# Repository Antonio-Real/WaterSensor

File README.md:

# **WaterSensor project**
 Wireless sensor for monitoring the level of a remote water tank.

 The motivation for this small home project came from the need to monitor the water level of a water tank used for watering. When the tank empties it causes air to fill the pipes and hoses, making it a bit of a pain to get out. With this system its easier to know when the tank is about to empty and flip a switch to turn on a water pump (in the future this system will automatically control the pump).

 ## **System overview**

In simple terms, the water level is read by a HC-SR04 ultrasonic sensor which works well on water and doesn't corrode like those contact sensors you dip into water. The sensor data is acquired by a ESP32 and sent to a second ESP32 in another location using ESP-NOW which works well over longer distances and has smaller overhead than WIFI. The water level is then displayed on a standard 16x02 LCD.

One of the challenges of the system came from the fact that the water tank is in a place with no power, so a solar panel made sense to power the sensor and microcontroller. A charge controller and a Lipo battery work together with the solar panel to regulate power to a stable 5V and provide power in periods of no sun. The ESP32 sender board was custom designed to have minimal components to save battery.

## **Materials/tools used**

- 5W Solar panel and solar power management module bought from [Waveshare](https://www.waveshare.com/solar-power-manager.htm).
- 1800 mAh Lipo battery.
- Custom designed ESP32 board.
- HC-SR04 Ultrasonic sensor.
- A second generic ESP32 board + 16x02 LCD.
- Creality Ender 3v2 for printing the enclosures for the PCB, sensor and power module to protect from dust.

## **Repository contents**

| Folder/Files           | Description                                                                          |
| ---------------------- | ------------------------------------------------------------------------------------ |
| [pcb](/pcb)            | Details and CAD files of the custom ESP32 board made for this project                |
| [firmware](/firmware)  | Firmware of both the receiver and sender ESP32 boards                                |
| [models](/models)      | STL files of the 3D printed parts for the enclosures                                 |

## **Pictures**

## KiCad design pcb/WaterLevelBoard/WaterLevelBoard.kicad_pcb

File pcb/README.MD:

# **Wireless sensor board**

This PCB design was kept to a minimum in order to optimize power consumption since it will function on a lipo battery. The main features:

- AP2112 3.3V low dropout (~50mV drop at 100mA) regulator to step down from the 5V that comes from the battery circuit.
- ESP32 microcontroller responsible for reading the HC-SR04 sensor and sending it through ESP-NOW protocol to a second ESP32.
- Screw terminals to easily connect the battery and the HC-SR04 ultrasonic sensor.

The PCB was designed using **Kicad 5.99** nightly build (soon to be released as Kicad 6).

 <br/><br/>

## **Schematic**

## **3D render of the PCB**

## **Manufactured PCB**
The PCB was manufactured in a PCB milling machine and unfortunately came out poorly and required some enameled wire to replace the damaged tracks.

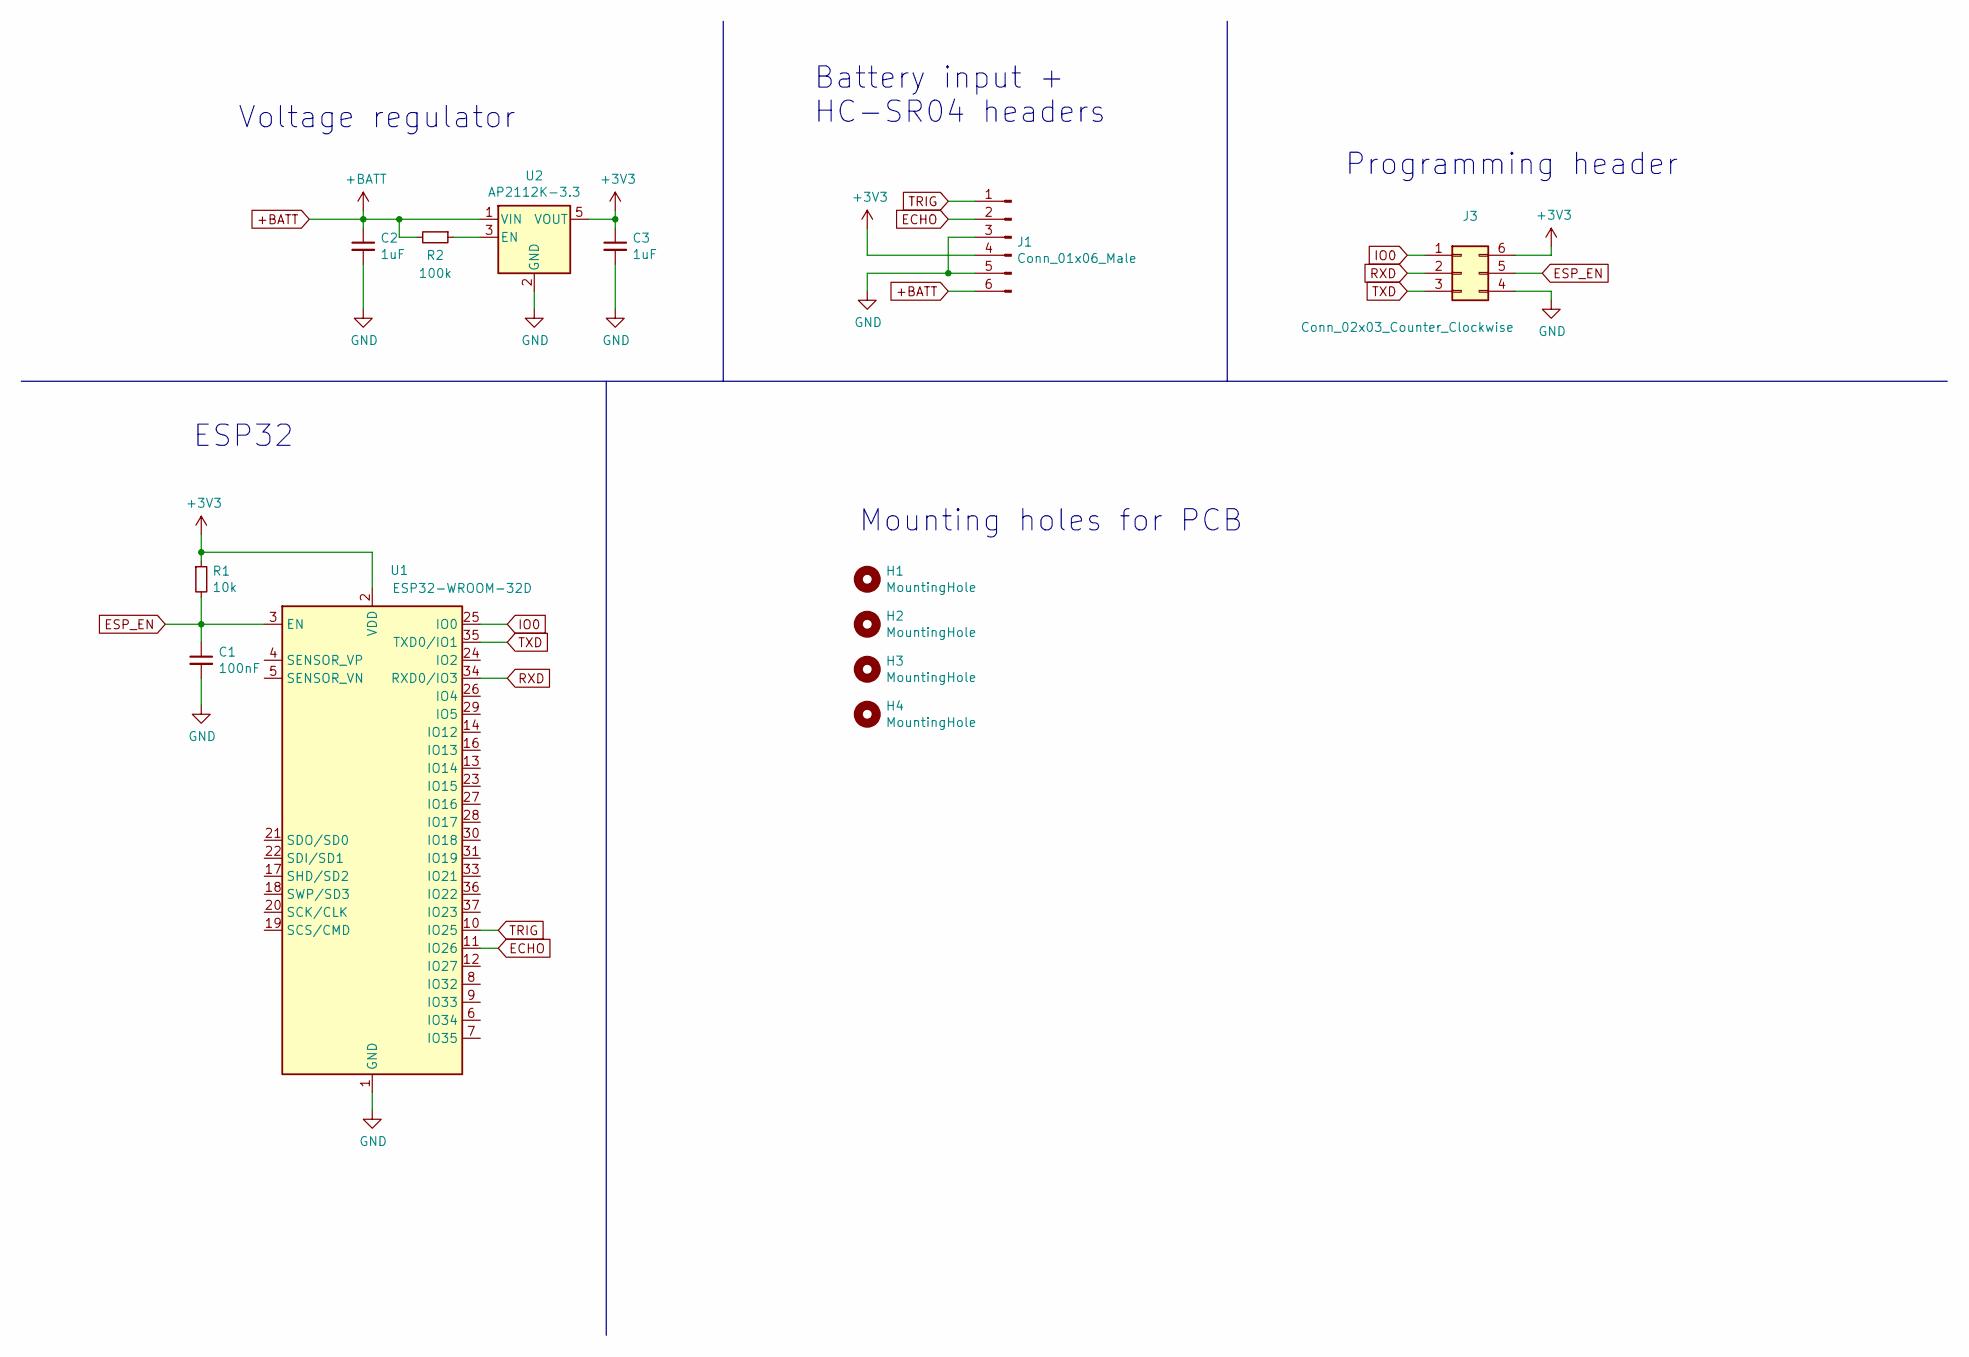
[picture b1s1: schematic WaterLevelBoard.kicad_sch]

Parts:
C1: 100nF; C_0603_1608Metric_Pad1.08x0.95mm_HandSolder
C2, C3: 1uF; C_0603_1608Metric_Pad1.08x0.95mm_HandSolder
H1, H2, H3, H4: MountingHole; MountingHole_2.1mm
J1: Conn_01x06_Male; TerminalBlock_Phoenix_MPT-0,5-6-2.54_1x06_P2.54mm_Horizontal
J3: Conn_02x03_Counter_Clockwise; PinHeader_1x06_P2.54mm_Vertical
R1: 10k; R_0603_1608Metric_Pad0.98x0.95mm_HandSolder
R2: 100k; R_0603_1608Metric_Pad0.98x0.95mm_HandSolder
U1: ESP32-WROOM-32D; ESP32-WROOM-32
U2: AP2112K-3.3; SOT-23-5

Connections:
+3V3: C3.1, J1.4, J3.6, R1.1, U1.2 (VDD), U2.5 (VOUT)
+BATT: C2.1, J1.6, R2.2, U2.1 (VIN)
ECHO: J1.2, U1.11 (IO26)
ESP_EN: C1.1, J3.5, R1.2, U1.3 (EN)
GND: C1.2, C2.2, C3.2, J1.3, J1.5, J3.4, U1.1 (GND), U1.15 (GND), U1.38 (GND), U1.39 (GND), U2.2 (GND)
IO0: J3.1, U1.25 (IO0)
unnamed: R2.1, U2.3 (EN)
RXD: J3.2, U1.34 (RXD0/IO3)
TRIG: J1.1, U1.10 (IO25)
TXD: J3.3, U1.35 (TXD0/IO1)

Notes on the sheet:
ESP32
Battery input + HC-SR04 headers
Mounting holes for PCB
Voltage regulator
Programming header

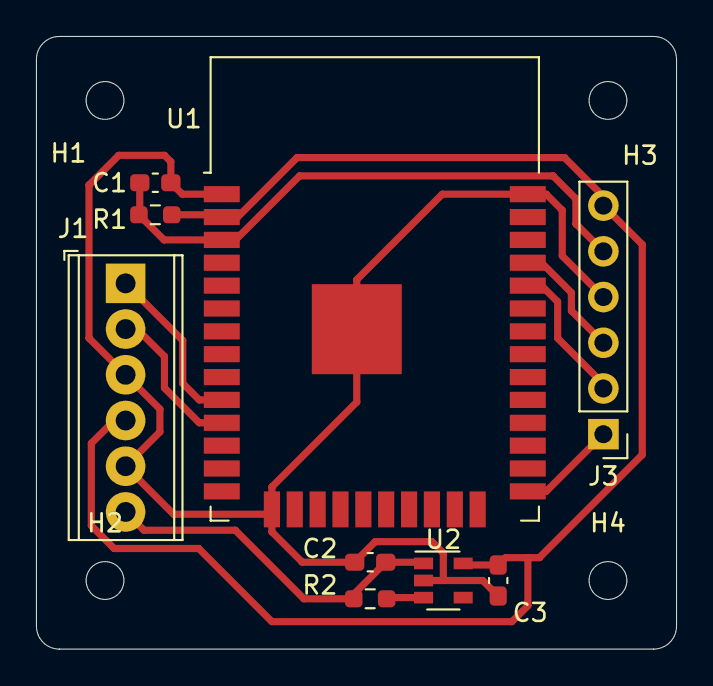
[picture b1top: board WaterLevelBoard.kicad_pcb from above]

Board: 2 copper layers, 35.6 x 34.0 mm, 13 parts (0 on the bottom side), 10 nets.

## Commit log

2021-11-27 Documented code and added README files to PCB and Firmware folders
2021-11-28 Added 3D models used and added READMES to all folders
